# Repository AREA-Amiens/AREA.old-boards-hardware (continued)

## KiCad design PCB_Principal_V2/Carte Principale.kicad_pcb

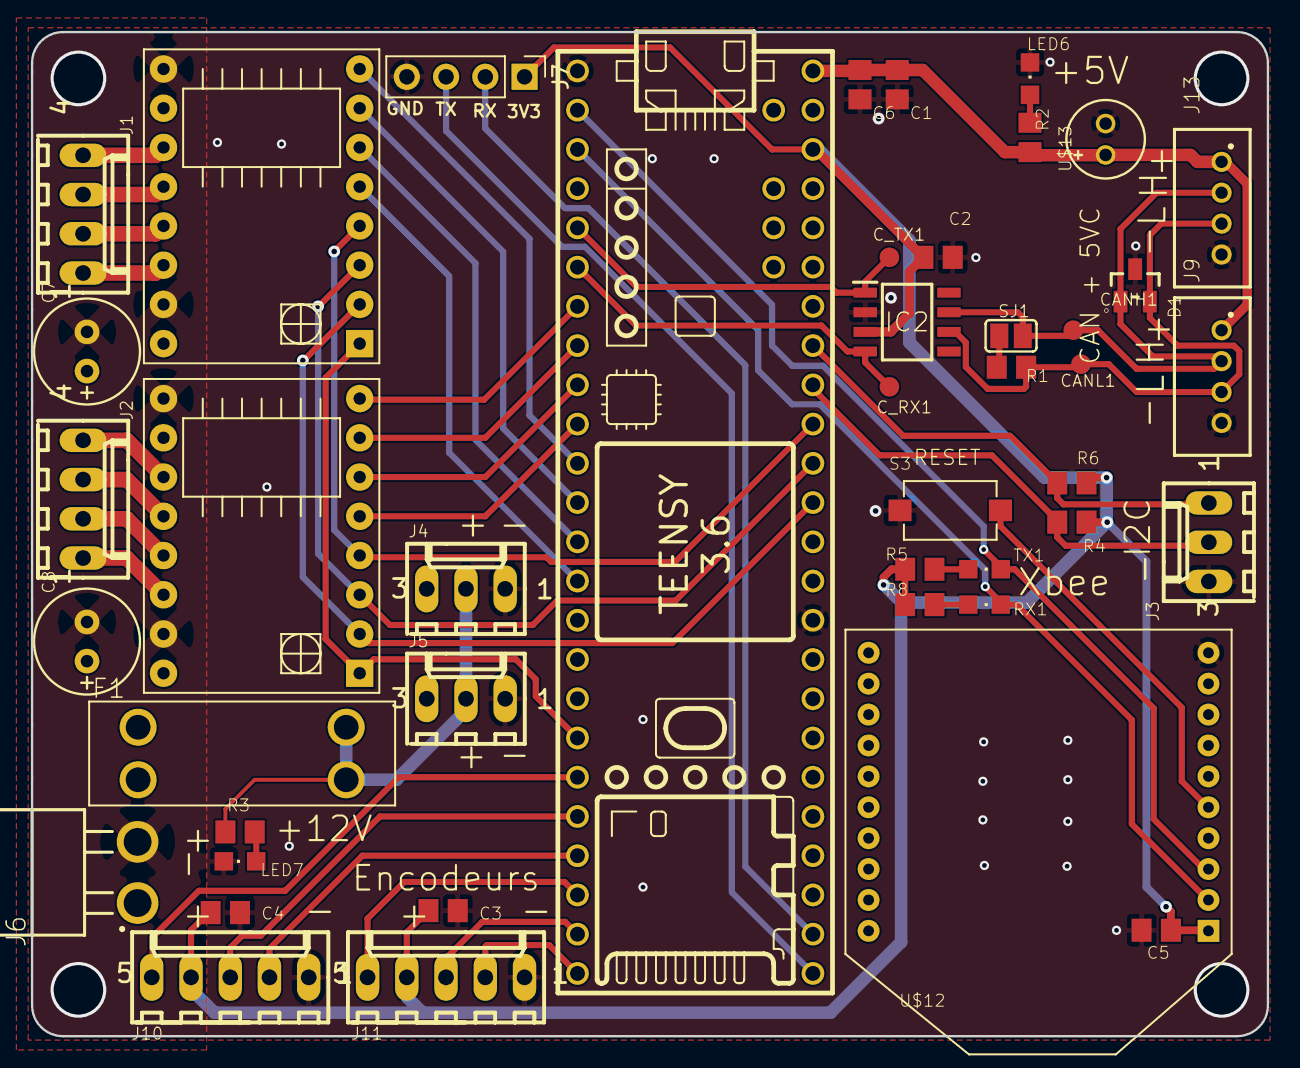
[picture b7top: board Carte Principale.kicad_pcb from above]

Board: 2 copper layers, 80.0 x 65.0 mm, 44 parts (0 on the bottom side), 47 nets.

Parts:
C1, C2, C3, C4, C5, C6: 100n; C0805
C7, C8: 100µ; E2,5-7
CANH1: TPB1,27; B1,27
CANL1: TPB1,27; B1,27
C_RX1: TPB1,27; B1,27
C_TX1: TPB1,27; B1,27
D1: 5Vdc; WE-TVS_SOT23-3L
F1: 3557-2; FUSE_3557-2
IC2: SN65HVD232D; SOIC127P600X175-8N
J1, J2: MOLEX_4DROIT; CON_4_DROIT
J3, J4, J5: MOLEX_3DROIT; CON_3_DROIT
J6: 645002117322
J7: Serial extern; PinHeader_1x04_P2.54mm_Vertical
J9, J13: 62000411622
J10, J11: 22-?-0527-2051; 6410-05
LED6, LED7: LEDCHIPLED_0805; CHIPLED_0805
R1: 120; R0805
R2, R3, R5, R8: R-EU_R0805; R0805
R4, R6: 4.7k; R0805
RX1: LEDCHIPLED_0805; CHIPLED_0805
S3: 434111025826
SJ1: SJ
TX1: LEDCHIPLED_0805; CHIPLED_0805
U$1, U$2: DRV8825
U$5: TEENSY_3.5_3.6_BASIC
U$12: XBEE
U$13: CONDO2-5; E2-5

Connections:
+3V3: C2.2, C3.1, C4.1, C5.1, IC2.3, J7.1, J10.4, J11.4, R4.2, R5.1, R6.2, R8.1, U$5.3V3_LO, U$12.1
+5V: C1.1, C6.1, J9.1, J13.1, R2.1, U$5.VIN, U$13.+
+12V: C7.+, C8.+, F1.3, F1.4, J4.2, J5.2, R3.1, U$1.P$16, U$2.P$16
/CANH: CANH1.TP, D1.1, IC2.7, J9.2, J13.2, SJ1.2
/CANL: CANL1.TP, D1.2, IC2.6, J9.3, J13.3, R1.1
/C_RX: C_RX1.TP, IC2.4, U$5.4/CANRX
/C_TX: C_TX1.TP, IC2.1, U$5.3/CANTX
/DIR_D: U$2.P$8, U$5.5
/DIR_G: U$1.P$8, U$5.9/CS
/ENABLE: U$1.P$1, U$2.P$1, U$5.26
/M0: U$1.P$2, U$2.P$2, U$5.15/A1
/M1: U$1.P$3, U$2.P$3, U$5.16/A2
/M2: U$1.P$4, U$2.P$4, U$5.17/A3
/RESET_D: U$2.P$5, U$5.8
/RESET_G: U$1.P$5, U$5.12/MISO
/RX_extern: J7.2, U$5.34/A15
/S1_D: J10.5, U$5.27
/S1_G: J11.5, U$5.30
/S2_D: J10.3, U$5.28
/S2_G: J11.3, U$5.31/A12
/S3_D: J10.2, U$5.29
/S3_G: J11.2, U$5.32/A13
/SLEEP_D: U$2.P$6, U$5.7
/SLEEP_G: U$1.P$6, U$5.11/MOSI
/STEP_D: U$2.P$7, U$5.6
/STEP_G: U$1.P$7, U$5.10/CS
/TX_extern: J7.3, U$5.33/A14
/µP_RX: RX1.C, U$5.1/TX, U$12.2
/µP_TX: TX1.C, U$5.0/RX, U$12.3
GND: C1.2, C2.1, C3.2, C4.2, C5.2, C6.2, C7.-, C8.-, D1.3, IC2.2, J3.3, J4.1, J5.1, J6.2, J7.4, J9.4, J10.1, J11.1, J13.4, LED6.C, LED7.C, S3.1, U$1.P$9, U$1.P$15, U$2.P$9, U$2.P$15, U$5.GND, U$5.GND2, U$12.10, U$13.-
unnamed: F1.1, F1.2, J6.1
unnamed: J1.1, U$1.P$14
unnamed: J1.2, U$1.P$13
unnamed: J1.3, U$1.P$12
unnamed: J1.4, U$1.P$11
unnamed: J2.1, U$2.P$14
unnamed: J2.2, U$2.P$13
unnamed: J2.3, U$2.P$12
unnamed: J2.4, U$2.P$11
unnamed: J3.1, R6.1, U$5.19/A5/SCL
unnamed: J3.2, R4.1, U$5.18/A4/SDA
unnamed: LED6.A, R2.2
unnamed: LED7.A, R3.2
unnamed: R1.2, SJ1.1
unnamed: R5.2, TX1.A
unnamed: R8.2, RX1.A
unnamed: S3.2, U$12.5

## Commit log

2020-11-26 First commit : Add lidar-boards and gatling-boards
2020-11-26 add Wurth connector and 3d file library
2021-04-12 Lib composant créée+pcb gatling mises à jours avec teensy (a verifier avant prod)
2021-04-12 prete pour inspection
2021-06-03 connect wire that weren't connected
2021-06-03 moving some traces
2021-06-03 Change dip switch for wurth dip sw
2021-06-25 add sensorv2 pcb
2021-06-25 add png and pdf files for sensor pcb
2021-07-12 Add V2 for pump PCB (9pump 9 Ev)
    TODO:
    - retrace CANbus properly
    - verify the wiring of the pump/ev
    - check for an alternative to the SN65HVD232D (CAN transceiver) wich is out of stock everywhere
2021-10-03 new PCB for 2022
2021-10-14 Add Rmeasure, Teensy AX12 and main PCB for the CDR2022
    -Rmeasure put in production on 13/10
    -Add UART to main pcb and rerouting can bus and swap tx/rx pin for the XBEE
    -new pcb with teensy 3.2, AX-12 connectivity, UART and CANbus
2021-10-19 ajout v3 carte alim
2021-10-25 some changes
2021-10-25 add MM connector + modification schematic pcb pump+ final routing IO
2021-10-31 add pcb esp32 + changes on pump pcb
2021-10-31 change connector and some final touch
2021-11-06 esp32 pas fini + silkscreen IO ok
2021-11-06 ESP32 fini
2021-11-06 mod esp32
2021-11-07 reroute some traces on ESP32 pcb
2021-11-07 change rgb on rmeasure + add library component
